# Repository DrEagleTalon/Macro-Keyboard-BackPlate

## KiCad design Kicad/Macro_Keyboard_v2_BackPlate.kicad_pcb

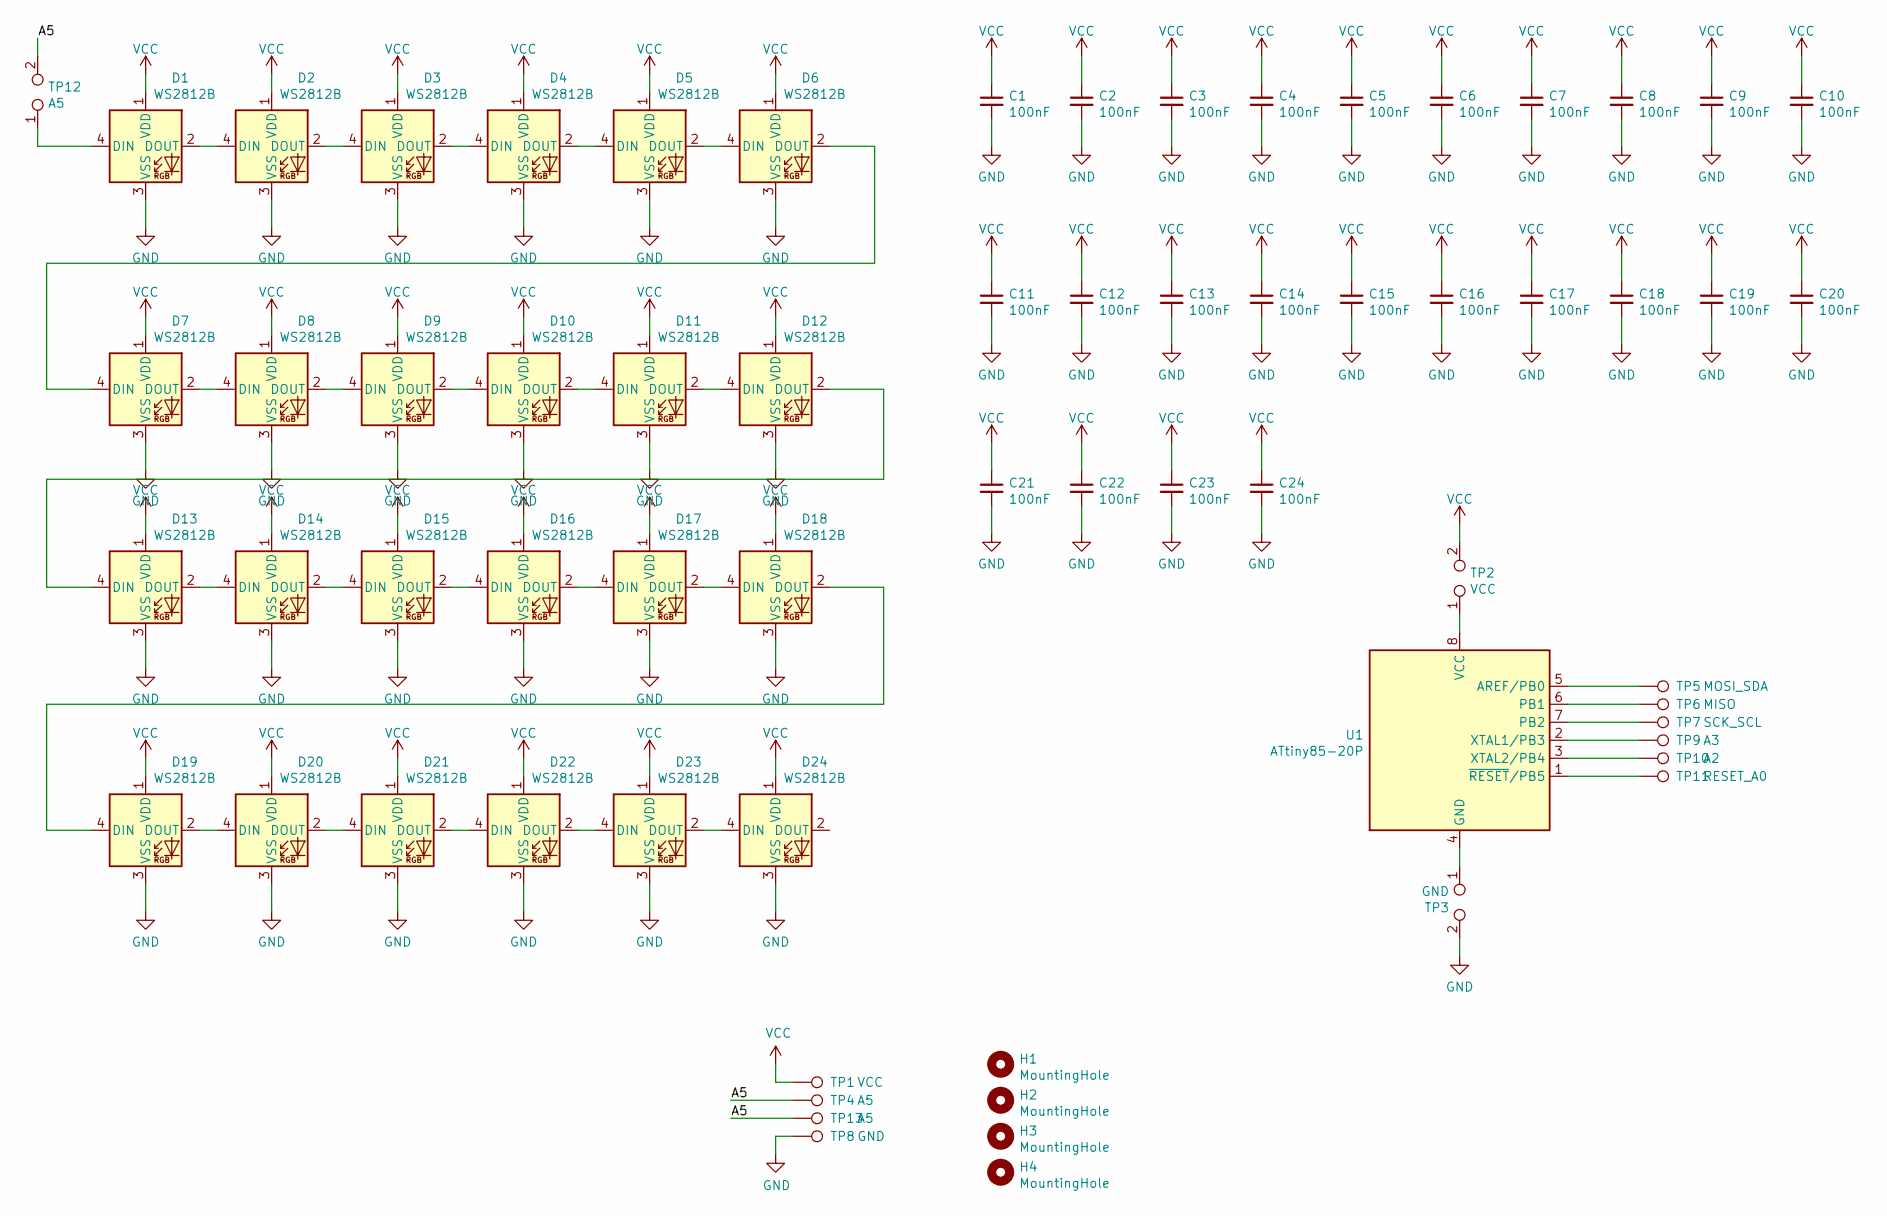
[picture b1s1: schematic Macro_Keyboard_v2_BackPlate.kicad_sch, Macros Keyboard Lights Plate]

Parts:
C1, C2, C3, C4, C5, C6, C7, C8, C9, C10, C11, C12, C13, C14, C15, C16, C17, C18, C19, C20, C21, C22, C23, C24: 100nF; C_0603_1608Metric; LCSC C14663
D1, D2, D3, D4, D5, D6, D7, D8, D9, D10, D11, D12, D13, D14, D15, D16, D17, D18, D19, D20, D21, D22, D23, D24: WS2812B; LED_WS2812B_PLCC4_5.0x5.0mm_P3.2mm; LCSC C114586
H1, H2, H3, H4: MountingHole; MountingHole_3.2mm_M3_DIN965_Pad
TP1: VCC; PinHeader_1x01_P2.54mm_Vertical
TP2: VCC; SolderJumper-2_P1.3mm_Open_RoundedPad1.0x1.5mm
TP3: GND; SolderJumper-2_P1.3mm_Open_RoundedPad1.0x1.5mm
TP4: A5; PinHeader_1x01_P2.54mm_Vertical
TP5: MOSI_SDA; TestPoint_Keystone_5015_Micro-Minature
TP6: MISO; TestPoint_Keystone_5015_Micro-Minature
TP7: SCK_SCL; TestPoint_Keystone_5015_Micro-Minature
TP8: GND; PinHeader_1x01_P2.54mm_Vertical
TP9: A3; TestPoint_Keystone_5015_Micro-Minature
TP10: A2; TestPoint_Keystone_5015_Micro-Minature
TP11: RESET_A0; TestPoint_Keystone_5015_Micro-Minature
TP12: A5; SolderJumper-2_P1.3mm_Open_RoundedPad1.0x1.5mm
TP13: A5; TestPoint_Keystone_5015_Micro-Minature
U1: ATtiny85-20P; DIP-8_W7.62mm

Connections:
/A5: TP4.1, TP12.2, TP13.1
GND: C1.2, C2.2, C3.2, C4.2, C5.2, C6.2, C7.2, C8.2, C9.2, C10.2, C11.2, C12.2, C13.2, C14.2, C15.2, C16.2, C17.2, C18.2, C19.2, C20.2, C21.2, C22.2, C23.2, C24.2, D1.3 (VSS), D2.3 (VSS), D3.3 (VSS), D4.3 (VSS), D5.3 (VSS), D6.3 (VSS), D7.3 (VSS), D8.3 (VSS), D9.3 (VSS), D10.3 (VSS), D11.3 (VSS), D12.3 (VSS), D13.3 (VSS), D14.3 (VSS), D15.3 (VSS), D16.3 (VSS), D17.3 (VSS), D18.3 (VSS), D19.3 (VSS), D20.3 (VSS), D21.3 (VSS), D22.3 (VSS), D23.3 (VSS), D24.3 (VSS), TP3.2, TP8.1
unnamed: D1.2 (DOUT), D2.4 (DIN)
unnamed: D1.4 (DIN), TP12.1
unnamed: D2.2 (DOUT), D3.4 (DIN)
unnamed: D3.2 (DOUT), D4.4 (DIN)
unnamed: D4.2 (DOUT), D5.4 (DIN)
unnamed: D5.2 (DOUT), D6.4 (DIN)
unnamed: D6.2 (DOUT), D7.4 (DIN)
unnamed: D7.2 (DOUT), D8.4 (DIN)
unnamed: D8.2 (DOUT), D9.4 (DIN)
unnamed: D10.2 (DOUT), D11.4 (DIN)
unnamed: D9.2 (DOUT), D10.4 (DIN)
unnamed: D11.2 (DOUT), D12.4 (DIN)
unnamed: D12.2 (DOUT), D13.4 (DIN)
unnamed: D13.2 (DOUT), D14.4 (DIN)
unnamed: D14.2 (DOUT), D15.4 (DIN)
unnamed: D15.2 (DOUT), D16.4 (DIN)
unnamed: D16.2 (DOUT), D17.4 (DIN)
unnamed: D17.2 (DOUT), D18.4 (DIN)
unnamed: D18.2 (DOUT), D19.4 (DIN)
unnamed: D19.2 (DOUT), D20.4 (DIN)
unnamed: D20.2 (DOUT), D21.4 (DIN)
unnamed: D21.2 (DOUT), D22.4 (DIN)
unnamed: D22.2 (DOUT), D23.4 (DIN)
unnamed: D23.2 (DOUT), D24.4 (DIN)
unnamed: TP2.1, U1.8 (VCC)
unnamed: TP3.1, U1.4 (GND)
unnamed: TP5.1, U1.5 (AREF/PB0)
unnamed: TP6.1, U1.6 (PB1)
unnamed: TP7.1, U1.7 (PB2)
unnamed: TP9.1, U1.2 (XTAL1/PB3)
unnamed: TP10.1, U1.3 (XTAL2/PB4)
unnamed: TP11.1, U1.1 (~RESET~/PB5)
VCC: C1.1, C2.1, C3.1, C4.1, C5.1, C6.1, C7.1, C8.1, C9.1, C10.1, C11.1, C12.1, C13.1, C14.1, C15.1, C16.1, C17.1, C18.1, C19.1, C20.1, C21.1, C22.1, C23.1, C24.1, D1.1 (VDD), D2.1 (VDD), D3.1 (VDD), D4.1 (VDD), D5.1 (VDD), D6.1 (VDD), D7.1 (VDD), D8.1 (VDD), D9.1 (VDD), D10.1 (VDD), D11.1 (VDD), D12.1 (VDD), D13.1 (VDD), D14.1 (VDD), D15.1 (VDD), D16.1 (VDD), D17.1 (VDD), D18.1 (VDD), D19.1 (VDD), D20.1 (VDD), D21.1 (VDD), D22.1 (VDD), D23.1 (VDD), D24.1 (VDD), TP1.1, TP2.2

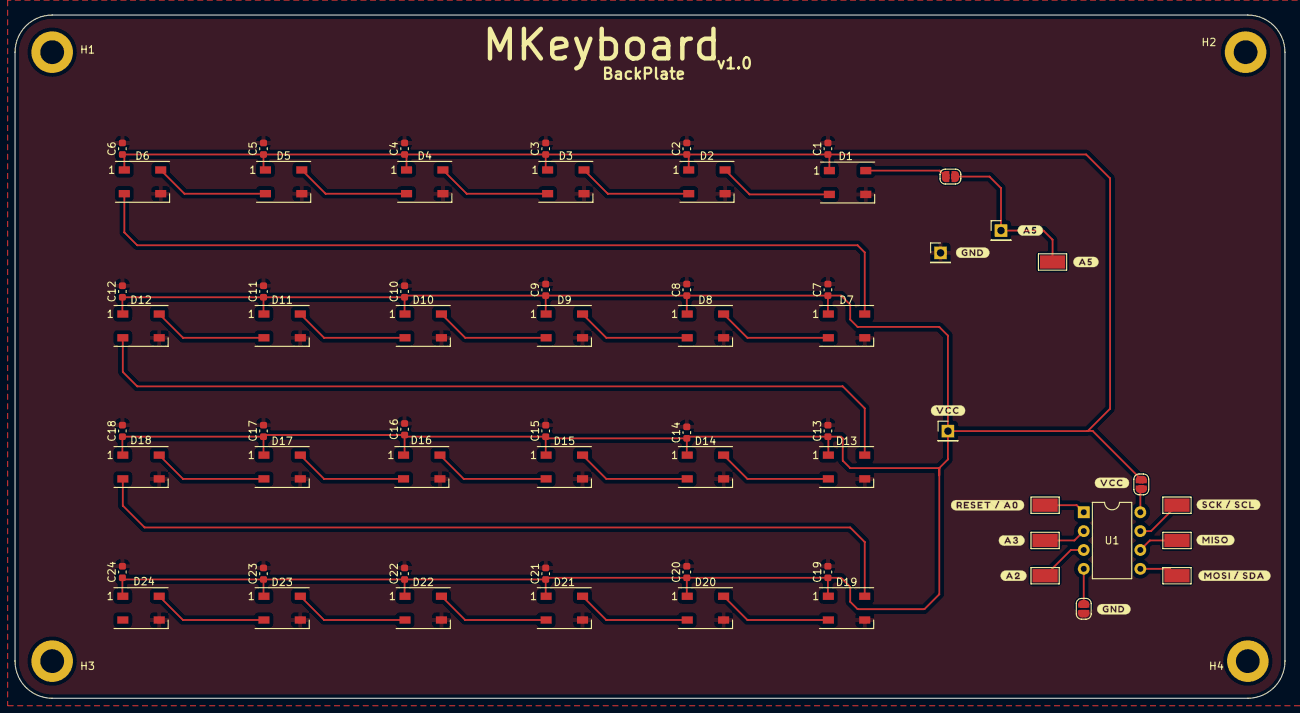
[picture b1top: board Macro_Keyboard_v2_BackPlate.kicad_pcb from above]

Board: 2 copper layers, 171.0 x 92.0 mm, 66 parts (0 on the bottom side), 35 nets.

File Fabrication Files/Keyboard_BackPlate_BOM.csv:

Comment,Designator,Footprint,LCSC
"100nF","C1,C2,C3,C4,C5,C6,C7,C8,C9,C10,C11,C12,C13,C14,C15,C16,C17,C18,C19,C20,C21,C22,C23,C24","Capacitor_SMD:C_0603_1608Metric","C14663"
"WS2812B","D1,D2,D3,D4,D5,D6,D7,D8,D9,D10,D11,D12,D13,D14,D15,D16,D17,D18,D19,D20,D21,D22,D23,D24","LED_SMD:LED_WS2812B_PLCC4_5.0x5.0mm_P3.2mm","C114586"
"MountingHole","H1,H2,H3,H4","MountingHole:MountingHole_3.2mm_M3_DIN965_Pad",""
"VCC","TP1","Connector_PinHeader_2.54mm:PinHeader_1x01_P2.54mm_Vertical",""
"A2","TP10","TestPoint:TestPoint_Keystone_5015_Micro-Minature",""
"RESET_A0","TP11","TestPoint:TestPoint_Keystone_5015_Micro-Minature",""
"A5","TP12","Jumper:SolderJumper-2_P1.3mm_Open_RoundedPad1.0x1.5mm",""
"A5","TP13","TestPoint:TestPoint_Keystone_5015_Micro-Minature",""
"VCC","TP2","Jumper:SolderJumper-2_P1.3mm_Open_RoundedPad1.0x1.5mm",""
"GND","TP3","Jumper:SolderJumper-2_P1.3mm_Open_RoundedPad1.0x1.5mm",""
"A5","TP4","Connector_PinHeader_2.54mm:PinHeader_1x01_P2.54mm_Vertical",""
"MOSI_SDA","TP5","TestPoint:TestPoint_Keystone_5015_Micro-Minature",""
"MISO","TP6","TestPoint:TestPoint_Keystone_5015_Micro-Minature",""
"SCK_SCL","TP7","TestPoint:TestPoint_Keystone_5015_Micro-Minature",""
"GND","TP8","Connector_PinHeader_2.54mm:PinHeader_1x01_P2.54mm_Vertical",""
"A3","TP9","TestPoint:TestPoint_Keystone_5015_Micro-Minature",""
"ATtiny85-20P","U1","Package_DIP:DIP-8_W7.62mm",""

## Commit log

2021-04-26 Clean Repo
